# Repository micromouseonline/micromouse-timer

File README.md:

# micromouse-timer
Hardware and software for a micromouse classic contest timing system

## Design goals
Many micromouse timing systems rely on devices placed in the posts to create a break-beam arrangement. An emitter in one post produces an optical signal that is detected by a matched receiver in the other post. Commercial break-beam devices are available from companies like Omron but they are very expensive, Simpler arrangements an be made with just an LED and phototransistor. For the most reliable operation, the measuring setup really needs to control both the emitter and detector synchronously so that it can detect the breaking of the beam under a wide range of ambient lighting conditions.

This need to connect one controller to both posts makes it necesary to get access to the posts from under the maze. Not only will that require the maze to be raised off the floor by some amount, it makes it very difficult to move the gates after the maze has been set up. Ideally, any timing system should not need any physical connections between components in the maze.

The APEC maze uses a gate sensor system that can be placed anywhere and only needs to be present on one side of the opening. It manages this by using a reflective sensor that measures the distance to the far post. These sensors are similar to those used in the popular Sharp distance sensors by they are have a much faster response time. The Sharp sensors canot be polled every milisecond to get high resolution timing. Unfortunately, making the reflective sensors is quite complicated and requires a certain amount of signal processing circuitry. It is not something that is terribly easy to reproduce.

When making a timing gate sensor, consideration must be given to the robots in the maze. They typically generate very high intensity pulses of IR or visible red light from multiple emitters at 1000Hz or more. Not only should the timing system be unaffected by these pulses, it should also not interfere with the robot's ablity to make measurements. Thus, the robot must not cause timing errors and the timing syste must not make the robots crash.

Finally, there is the issue of ambient lighting levels. These are variable from venue to venue and may vary greatly even during a contest. A venue with natural light may have direct sunlight into the room and, clearly, that light will move around during the day. Other sources of interfering ambient light might include camera lights and camera flashguns. theese too should not interfere with the operation of the timing system.

With so many constraints, it would be natural to seek ever more sophisticated solutions to overcome them.

After several experiments with 'clever' designs, this project tries to make everything as simple as possible.

## Components
There are four components for this timing system
1. gate emitters  - these are just blue LEDs connected to a single Lithium cell with a single current limit resistor. They operate continuously for up to 36 hours between charges.
2. gate receivers - these have a phototransistor with a single load resistor connected to an analogue input channel on an Arduino. The Arduino is also connected to a small 433MHz radio module so that it can send detected changes to a timing controller. Again, a single Lithium cell provides power for at least 20 hours operation.
3. gate controller - the controller is connected directly to the timing management computer with a USB-serial link. It also has a radio receiver so that it can obtain event information from the gate receivers. Each gate receiver sends encoded packets to identify the event and the gate ID. The controller performs the actual timing function and all the data can be stored on an SD card for independent operation or to provide a backup. Power can come from the host USB connection, batteries or a separate power supply. Optionally, a Bluetooth conenction could be made to the host. Sinca all the communication with the gates is wireless, the controller can be placed several metres away from the maze and there are no trailing wires to the maze.
4. timing manager - the software running on the host computer that accepts timing information from the controller, presents it on the display screens and maintains the contest results.

## Gate Operation
Each gate has an emitter and a receiver.

### Emitters
The emitter generates a continuous beam of illumination using blue light. Green light would be a good alternative. While apparently very bright to the human eye, typical micromouse sensor will be relatively insensitive to these wavelengths and, in any case, will perceive the illumnation as part of the background and so it should be compensated for. Blue LEDs have quite high forward voltages of around 2.8 to 3.0 Volts but can still be run from a single Lithium cells with a small series current limiting resistor. Using a resistor value of 39 Ohms with the chosen device limits the maximum current to around 27mA with a fully charged battery at 4.2Volts. As the battery discharges to a nominal 3.7 Volts, the current decreases to about 15mA.

The battery is a Nokia BL-4S with a nominal capacity of 860 mAhr. Once turned on, there should be sufficient capacity for at least 36 hours operation.

A TP4056-based battery charge and protect circuit prevents over discharge of the battery and allows for easy re-charging from a 5V source such as a cell-phone charger of portable power bank.

The emmitter assembly is entirely contained within a typical plastic classic wall. Light shines through a hole in the end of the wall and a corresponding hole is a post. Where the gate must be perpendicular to the wall, a special post is used that contains an embedded reflector at 45 degrees. The reflecto involves a failry large aamount of light loss but is still sufficent for the task. Straight-through emitters might benefit from lower intensity and this could be provided with an additional switch to change the current limit resistor.

### Detectors
The detector circuit is minimal. It consistes of a TEPT5600 visible light phototransistor with a 2200Ohm load resistor on the emitter. The transistor emitter is connected directly to an analogue channel on an arduino mini-pro. The load resistor is selected to give a reading of between 20 and 60 counts when illuminated only by the LED in the timing gate in its normal operating configuration. This is quite a low sensitivity but it ensures that operation will be relatively unaffected even by quite bright ambient illumination right up to the point of saturation of the phototransistor

Attached to a software serial TX pin on the Arduino is a self-contained radio transeiver used only in its transmit mode. the radio is powered down until the gate is interrupted. When messages are to be sent, the radio is powered up, placed in transmit mode and the message is transmitted several times to ensure reliable communication. Aferards, the radio is powered down again to reduce current consumption and prevent interference.

All the radios in the system operate on the same frequency but there should be no natural circumstance where more than one transmits at a time. Thus, the controller needs only one radio and can distinguish the message source from its content.

Like the emitter, the circuitry all fits inside a typical classic maze wall and runs from a BL-4S battery using the same type of TP4056 charge/protect module. In normal operation, the Arduino draws only 12mA and the brief periods of transmission double that for a second or two. Continuous operation should be possible for at least 50 hours with a fully charged BL-4S battery.

### Controller
At the heart of the timing operation is the controller. An Arduino is connected to another LINX radio module which is running continuously in receive mode. It listens for packets from the gate detectors and runs a state machine that looks after all the timing functions related to the current contest.

While intended primarily for micromouse, the same controller could be used for drag race, line follower and time trial contests. Some additional care would be needed to distinguish the transmissions from gates in other contests. The controller passes timing and event notfications to the host computer running event management software using a USB-serial bridge. The same connection can provide power.

So that the controller can be used stand-alone and/or act as a backup to automatic timing, it also has an LCD display and a number of manual buttons that set the state of the system and provide manual gate inputs if needed.

Internally, an SD card records all the incoming and outgoing messages so that they can be retreived for later analysis and toserve as an auxiliary store in case of an error or failure in the management software. Files are time stamped using a data from a battery-backed real time clock module. Note that the RTC battery is not rechargeable and annual maintenance should be carried out to replace the battery and ensure thatthe time and date are correct.

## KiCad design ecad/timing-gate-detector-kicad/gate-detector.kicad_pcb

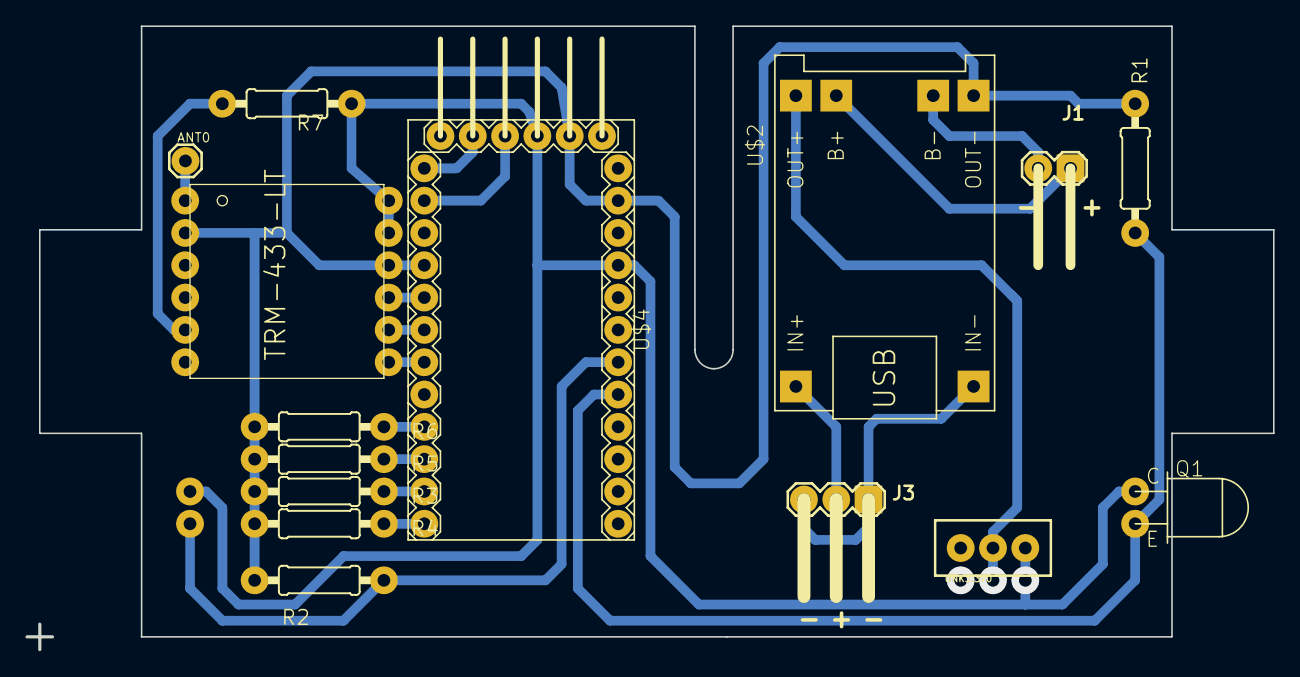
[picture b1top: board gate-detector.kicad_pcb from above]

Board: 6 copper layers, 97.9 x 48.9 mm, 16 parts (1 on the bottom side), 20 nets.

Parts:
ANT0: M01PTH; 1X01
J1: LiPo Cell; 1X02_RA_PTH_MALE_MILL
J3: 5V charge; 1X03_RA_PTH_MILL
Q1, Q2: TEPT5600; PHOTOTRANSISTOR-TO5-SIDE
R1, R2, R3, R4, R5, R6: 2k2; AXIAL-0207_0.4
R7: 1M0; AXIAL-0207_0.4
U$1: TRM-433-LT; LINX-TRM-433-LT
U$2: BATTERY-CHARGER-LI-PROT
U$4: ARDUINO-PRO-MINI-PROG
UNK3.3V0: SWITCH_SPDT_PTH_11.6X4.0MM_KIT

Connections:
3.3V: U$2.OUT+, UNK3.3V0.2
ANT*: ANT0.1, U$1.ANT
DATA: U$1.DATA, U$4.D4
GND: R1.1, R2.1, R3.1, R4.1, R5.1, R6.1, U$1.GND, U$1.GND@2, U$2.OUT-, U$4.GND@1, U$4.GND@2, U$4.GND@3
unnamed: Q2.E, R2.2, U$4.A1
unnamed: J1.1, U$2.B+
unnamed: R4.2, U$4.D9
unnamed: R3.2, U$4.D8
unnamed: R5.2, U$4.D7
unnamed: Q1.E, R1.2, U$4.A0
unnamed: J1.2, U$2.B-
unnamed: R6.2, U$4.D6
unnamed: R7.2, U$1.AREF
unnamed: J3.2, U$2.IN+
unnamed: J3.1, J3.3, U$2.IN-
unnamed: U$4.TX0@2, U$4.TX1@1
unnamed: U$4.RX0@1, U$4.RX1@2
PDN: U$1.PDN, U$4.D2
TX: U$1.T/~R, U$4.D3
VCC: Q1.C, Q2.C, R7.1, U$1.LADJ, U$1.VCC, U$4.VCC@1, U$4.VCC@2, UNK3.3V0.3

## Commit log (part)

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2019-12-28 add emitter schematic
2019-12-29 update detector schematic
2020-01-02 add gate controller schematic
2020-01-05 update gate controller schematics
2020-01-06 add LED display
2020-01-07 remove LED display
2020-01-07 add pullups and re-arrange buttons
2020-01-08 tidy the controller schematic a little
2020-01-13 images of the first prototype
2020-01-13 add a picture readme.md
2020-01-15 resize images of the first prototype
2020-01-16 first code commit
2020-01-16 Update the readme files
2020-01-16 Add a README to the code folder
2020-01-17 tidy up code and reduce footprint
2020-02-03 update pictures and code
2020-02-13 new pictures
2020-02-13 resize pictures
2022-06-11 update gitignore files
2022-06-11 track travis file
2022-06-11 reformat and organise gate-controller
2022-06-11 update all the images
2022-06-11 update PDF files
2022-06-11 update readme and license files
2022-06-11 update the build scripts
2022-06-11 reorganise gate detector
2022-06-11 reorganise radio RX test
2022-06-11 reorganise radio TX test
2022-06-11 reorganise SD card test
2022-06-11 update description of messages used
2022-06-11 add constants for new message set
2022-06-18 add linx radio data sheet and app note
2022-06-18 many changes to controller
2022-06-18 update the valid messages
2022-06-18 set the port used for the controller
2022-06-18 simplify the gate detector
2022-06-18 update the basic radio tests
2022-06-18 fix overflow error in keritimer
2022-06-20 remove old message definitions
2022-06-20 track the combined state of the buttons
2022-06-20 remove old state definitions
2022-06-20 add facility to reset controller from buttons
2022-06-20 update new mouse message
2022-06-20 define radio pins symbolically
2022-06-20 rework startup sequence
2022-06-20 update for time trials
2022-06-20 don't track encoder button state
2022-06-20 refactor contest type selection
2022-06-20 move some code around
2022-06-20 remove unused code
2022-06-20 move some doc files
2022-06-20 simplify the button class
2022-06-20 and a little tidy of button.h
2022-06-20 add time trial option
2022-06-22 remive unused files
2022-06-22 remove dead code
2022-06-22 rename gate message reader
2022-06-22 clear maze time when new mouse selected
2022-06-22 clean up trial_machine a little
2022-06-22 add comment about ST_GOAL state
2022-06-22 rename gate message time variable
2022-06-23 improved controller code
2022-06-23 improved detector code
2022-06-23 update version on menu
2022-07-13 tighten up the message timing
2022-07-13 improve the startup indication
2023-07-05 add all project files to repository
2023-07-13 Allow fast recovery and occlusion protection
2024-06-26 reset waits for button release
2024-06-26 only send the time once
2024-06-26 gives the radio data state names instead of numbers
2024-06-26 show state whenever it changes
2024-06-26 add comments to messages
2024-07-06 add watchdog message type
2024-07-06 send watchdog message every second
2024-07-06 reset defaults to maze timer reset with button down to change mode
2024-07-06 defines the reset vector more flexibly
2024-07-06 messages are explititly used inline
2024-07-17 create a vscode workspace
2024-07-17 go back to automatic port detection for windows
2024-07-17 add clang-format config
2024-07-17 change the message order
2024-07-17 prevent multiple messages when pressing two buttons
2024-07-18 make the gate tag available globally
2024-07-18 initialise gate tag to a known value
2024-07-18 add some commented debug messages
2024-07-18 skip run times of less than 500ms
